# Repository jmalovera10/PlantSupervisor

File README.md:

# PlantSupervisor
This is an IoT project intended to monitor and control crops. Here you may find the PCB designed for this purpose and the code written for the controller.

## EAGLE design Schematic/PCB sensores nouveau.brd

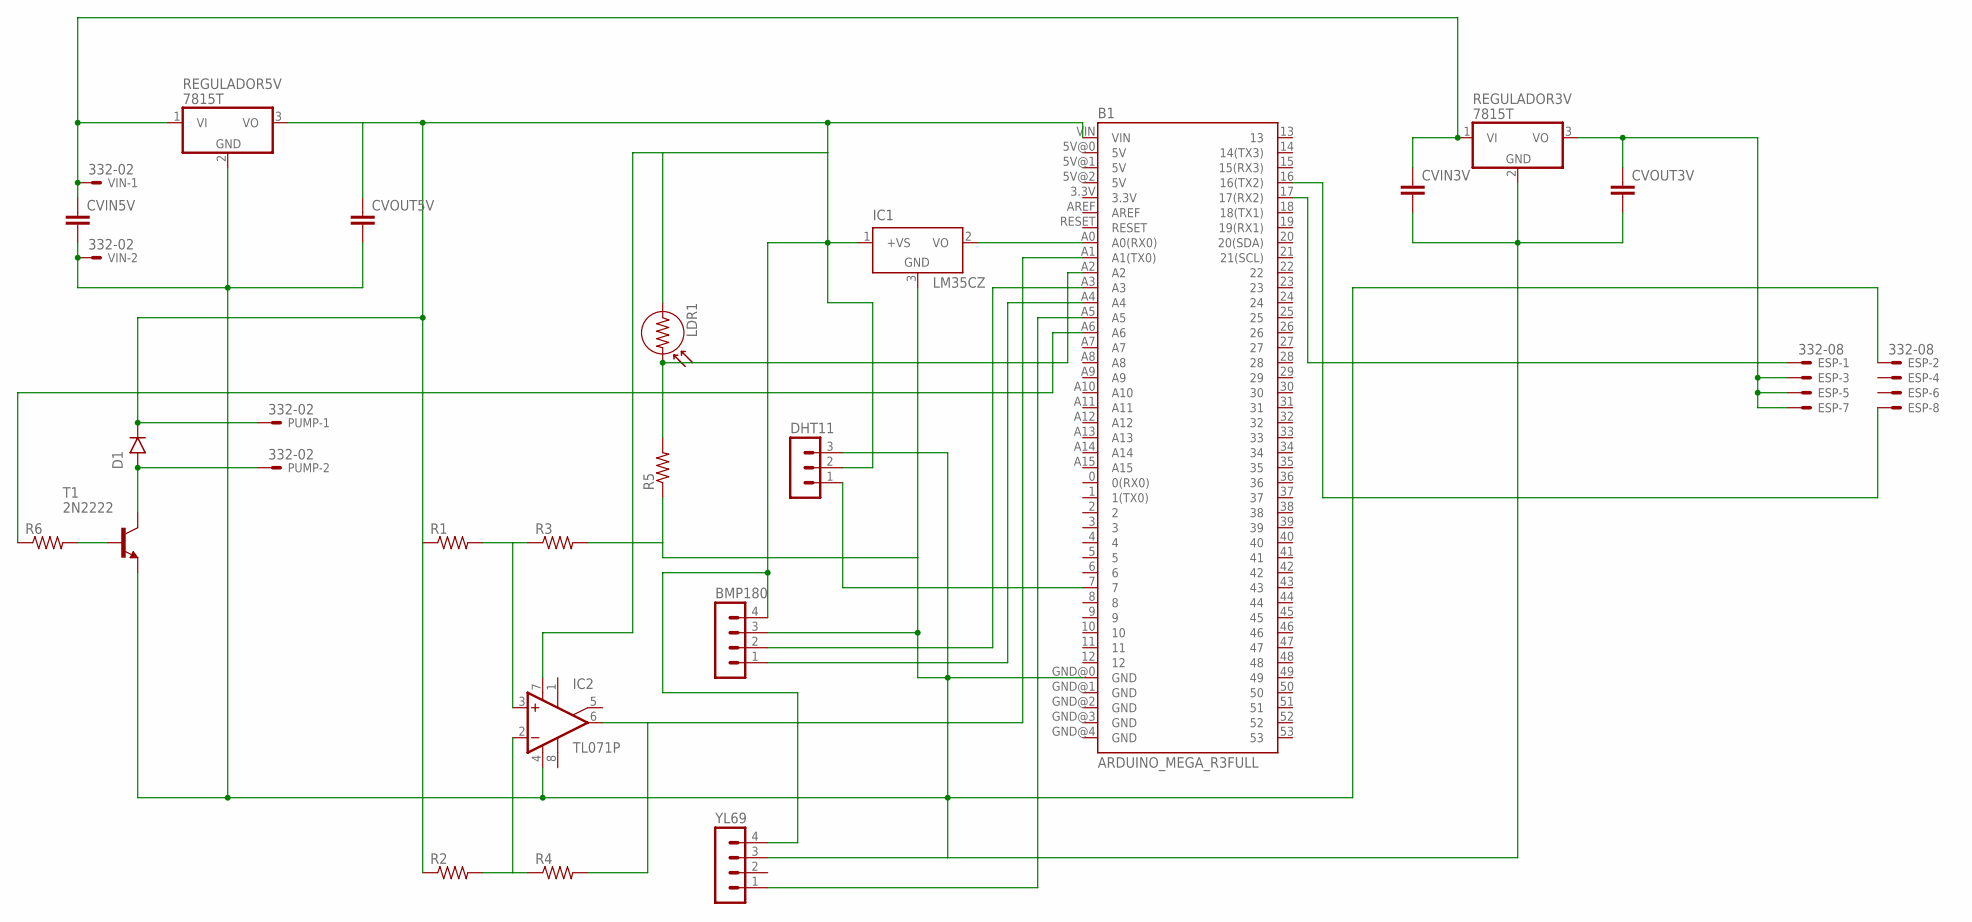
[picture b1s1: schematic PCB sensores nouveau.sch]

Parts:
B1: ARDUINO_MEGA_R3FULL; ARDUINO_MEGA
BMP180: MA04-1
CVIN3V, CVIN5V: C2,5-3; C2.5-3
CVOUT3V, CVOUT5V: C2,5-3; C2.5-3
D1: 1N4001; DO41-10
DHT11: MA03-1
ESP: 332-08
IC1: LM35CZ; TO92
IC2: TL071P; DIL08
LDR1: LDR
PUMP: 332-02
R1, R2, R3, R4, R5, R6: R-US_0207/10; 0207/10
REGULADOR3V, REGULADOR5V: 7815T; TO220H
T1: 2N2222; TO18
VIN: 332-02
YL69: MA04-1

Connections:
unnamed: B1.GND@0 (GND), BMP180.3, CVIN5V.2, CVOUT5V.2, DHT11.3, ESP.2, IC1.3 (GND), IC2.4 (V-), R3.2, R5.1, REGULADOR5V.2 (GND), T1.1 (E), VIN.2, YL69.3
unnamed: B1.7, DHT11.1
unnamed: IC2.2 (-IN), R2.2, R4.1
unnamed: B1.A2, LDR1.2, R5.2
unnamed: CVOUT3V.1, ESP.3, ESP.5, ESP.7, REGULADOR3V.3 (VO)
unnamed: B1.A3, BMP180.2
unnamed: B1.A0 (A0(RX0)), IC1.2 (VO)
unnamed: B1.A4, BMP180.1
unnamed: CVIN3V.1, CVIN5V.1, REGULADOR3V.1 (VI), REGULADOR5V.1 (VI), VIN.1
unnamed: B1.VIN, BMP180.4, CVOUT5V.1, D1.C (CATHODE), DHT11.2, IC1.1 (+VS), IC2.7 (V+), LDR1.1, PUMP.1, R1.1, R2.1, REGULADOR5V.3 (VO), YL69.4
unnamed: B1.A5, YL69.1
unnamed: IC2.3 (+IN), R1.2, R3.1
unnamed: CVIN3V.2, CVOUT3V.2, REGULADOR3V.2 (GND)
unnamed: B1.A1 (A1(TX0)), IC2.6 (OUT), R4.2
unnamed: R6.2, T1.2 (B)
unnamed: B1.A6, R6.1
unnamed: D1.A (ANODE), PUMP.2, T1.3 (C)
unnamed: B1.17 (17(RX2)), ESP.1
unnamed: B1.16 (16(TX2)), ESP.8

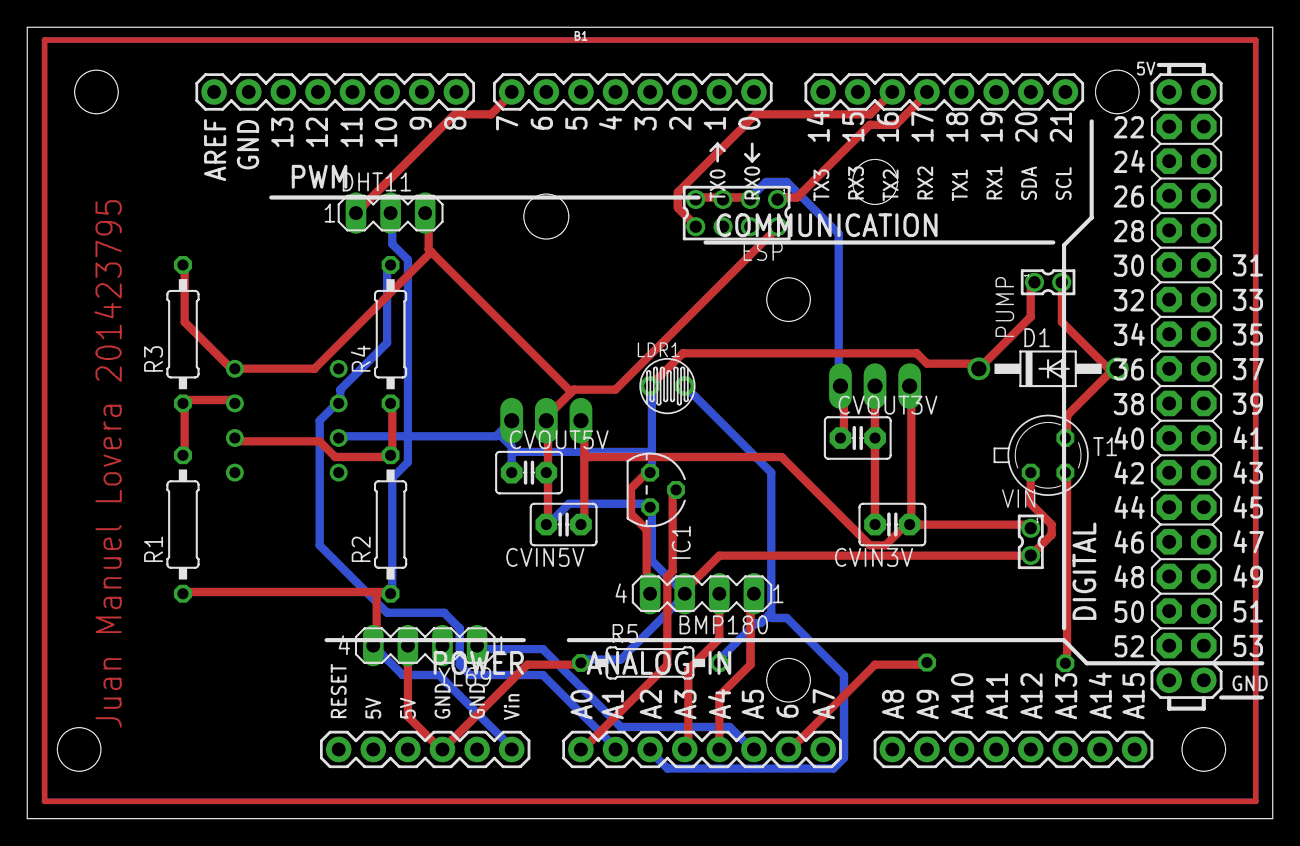
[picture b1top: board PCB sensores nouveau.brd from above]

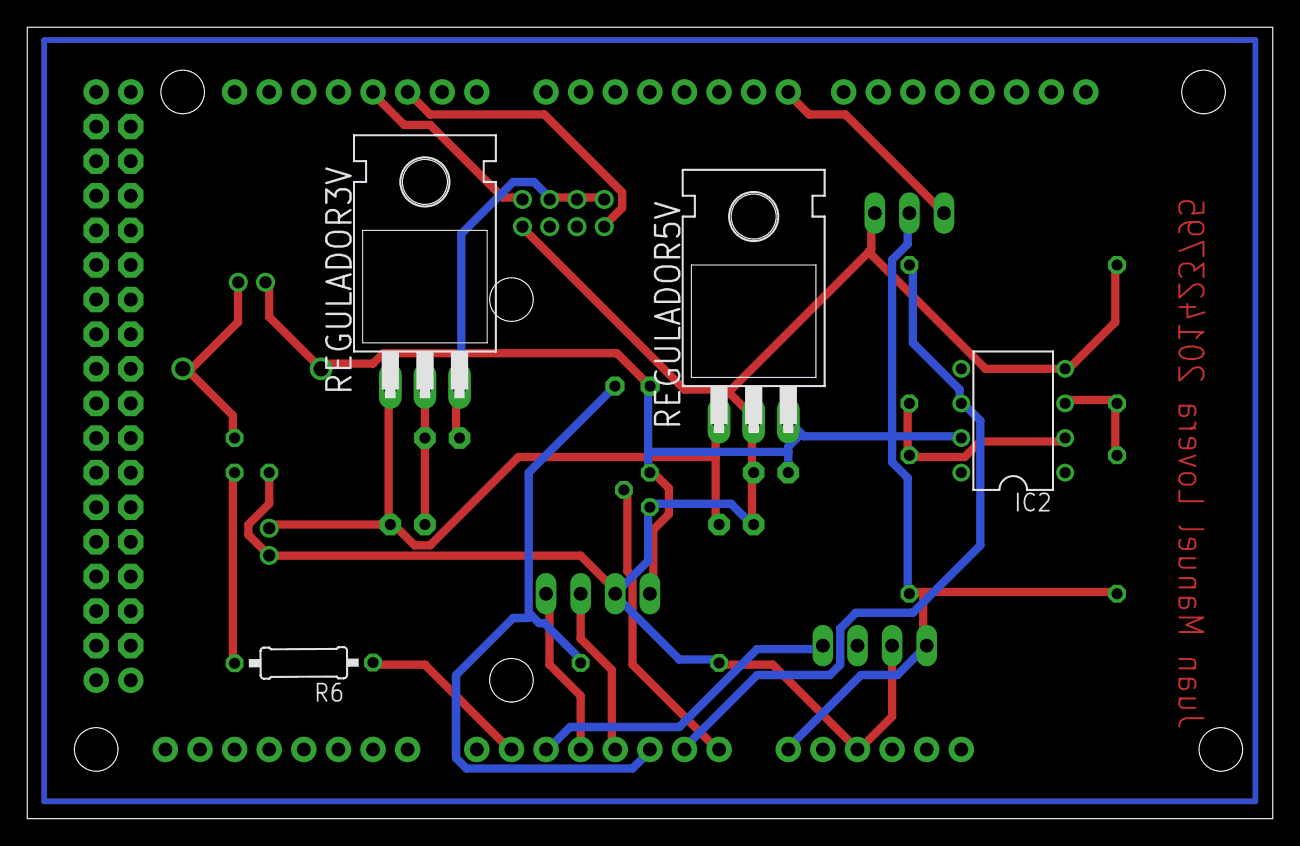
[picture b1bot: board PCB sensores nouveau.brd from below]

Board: 2 copper layers, 91.4 x 58.1 mm, 24 parts (4 on the bottom side), 19 nets.

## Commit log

2018-05-27 Half sensor values
2018-05-28 Advance
2018-05-29 Webpage
2018-05-29 Page fundamentals add arduino
2018-05-29 BMP update

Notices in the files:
parts and their libraries:
SparkFun-Boards: Licensing: Creative Commons ShareAlike 4.0 International - https://creativecommons.org/licenses/by-sa/4.0
